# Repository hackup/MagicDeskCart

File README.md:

# MagicDeskCart

The MagicDeskCart is a simple bank switching cartridge for the C64/C128. It is a rendition of a ["Magic Desk"](https://csdb.dk/release/?id=132937) compatible layout. There is also no warranty whatsoever. **USE AT YOUR OWN RISK!**.

**WARNING**: In revision 1, the jumper labels have been accidentally reversed!

See my [blog post](https://www.hackup.net/2019/07/bank-switching-cartridges/) for more details.

## License
Released under GNU General Public License v3.0, see LICENSE file.

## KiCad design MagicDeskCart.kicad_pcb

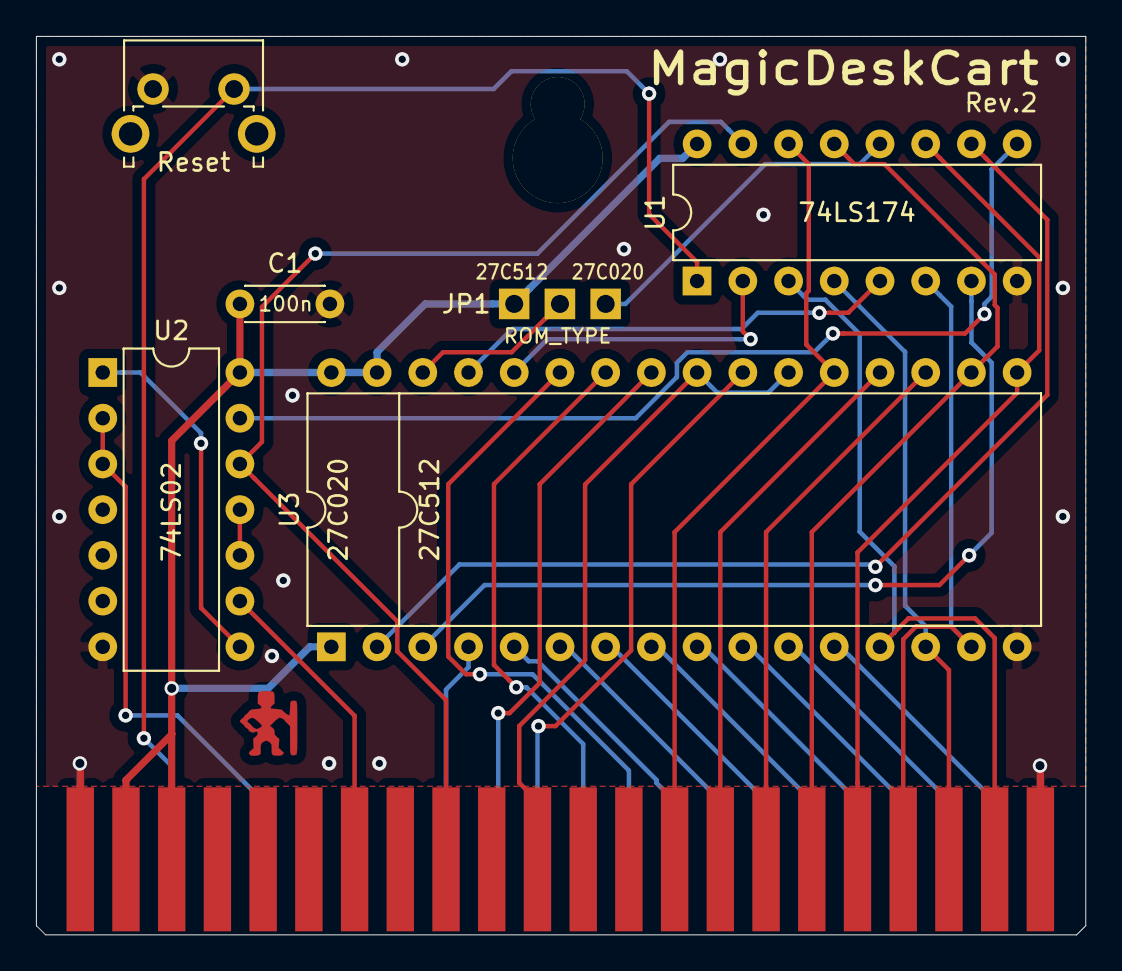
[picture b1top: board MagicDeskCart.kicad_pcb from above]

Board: 2 copper layers, 58.3 x 49.9 mm, 7 parts (0 on the bottom side), 37 nets.

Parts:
C1: 100n; C_Disc_D4.3mm_W1.9mm_P5.00mm
JP1: ROM_TYPE; Pin_Header_Straight_1x03_Pitch2.54mm
SW1: Reset; SW_Tactile_SPST_Angled_PTS645Vx83-2LFS
U1: 74LS174; DIP-16_W7.62mm
U2: 74LS02; DIP-14_W7.62mm
U3: 27C020; DIP-32_W15.24mm
U4: C64-Exp-Port; C64-Cart-NoSilkS

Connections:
+5V: C1.1, JP1.3, U1.16, U2.14, U3.1, U3.31, U3.32, U4.2, U4.3
/A0: U3.12, U4.Y
/A1: U3.11, U4.X
/A2: U3.10, U4.W
/A3: U3.9, U4.V
/A4: U3.8, U4.U
/A5: U3.7, U4.T
/A6: U3.6, U4.S
/A7: U3.5, U4.R
/A8: U3.27, U4.P
/A9: U3.26, U4.N
/A10: U3.23, U4.M
/A11: U3.25, U4.L
/A12: U3.4, U4.K
/D0: U1.3, U3.13, U4.21
/D1: U1.4, U3.14, U4.20
/D2: U1.6, U3.15, U4.19
/D3: U1.11, U3.17, U4.18
/D4: U1.13, U3.18, U4.17
/D5: U3.19, U4.16
/D6: U3.20, U4.15
/D7: U1.14, U3.21, U4.14
/DIS: U1.15, U2.12, U4.9
/EN: U1.9, U2.13
/S13: U1.2, U3.28
/S14: U1.5, U3.29
/S15: U1.7, U3.3
/S16: U1.10, U3.2
/S17: JP1.1, U1.12
GND: C1.2, SW1.1, U1.8, U2.7, U3.16, U4.1, U4.22, U4.A, U4.Z
unnamed: JP1.2, U3.30
unnamed: SW1.2, U1.1, U4.C
unnamed: U2.1, U2.8
unnamed: U2.2, U2.3, U4.E
unnamed: U2.9, U4.7
unnamed: U2.10, U2.11
unnamed: U3.22, U3.24, U4.11

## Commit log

2019-05-13 Initial import.
2019-05-13 Mapped footprints.
2019-05-13 Preparing for board layout.
2019-05-13 Routing.
2019-06-13 Mixed up the jumper labels again, damn it!
2019-07-09 Added readme.
2019-07-09 Fixed media link.
2019-07-11 Updated readme.
